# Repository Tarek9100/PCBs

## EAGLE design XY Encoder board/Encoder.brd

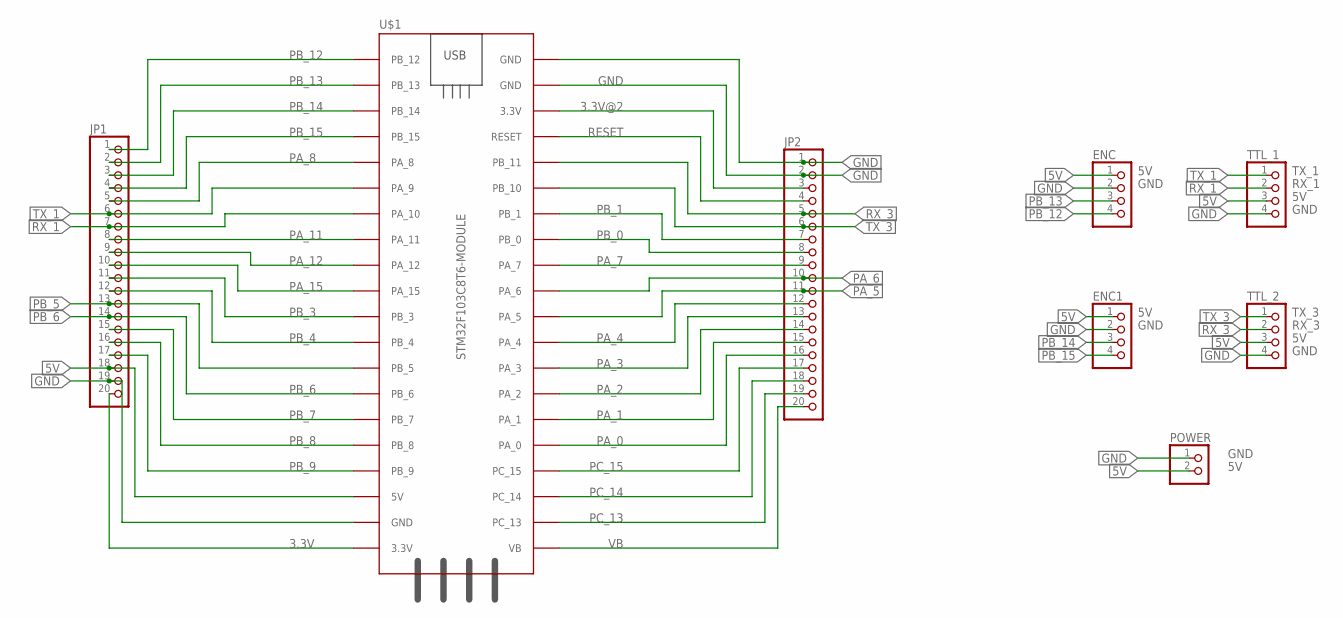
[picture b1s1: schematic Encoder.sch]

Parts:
ENC, ENC1: PINHD-4_DATA; 1X04_DATA
JP1, JP2: PINHD-1X20; 1X20
POWER: PINHD-2_DATA; 1X02_DATA
TTL_1, TTL_2: PINHD-4_DATA; 1X04_DATA
U$1: STM32F103C8T6-MODULE

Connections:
3.3V: JP1.20, U$1.3.3V_1 (3.3V)
3.3V@2: JP2.3, U$1.3.3V_2 (3.3V)
5V: ENC.1, ENC1.1, JP1.18, POWER.2, TTL_1.3, TTL_2.3, U$1.5V
GND: ENC.2, ENC1.2, JP1.19, JP2.1, JP2.2, POWER.1, TTL_1.4, TTL_2.4, U$1.GND_1 (GND), U$1.GND_2 (GND), U$1.GND_3 (GND)
PA_0: JP2.16, U$1.PA_0
PA_1: JP2.15, U$1.PA_1
PA_2: JP2.14, U$1.PA_2
PA_3: JP2.13, U$1.PA_3
PA_4: JP2.12, U$1.PA_4
PA_5: JP2.11, U$1.PA_5
PA_6: JP2.10, U$1.PA_6
PA_7: JP2.9, U$1.PA_7
PA_8: JP1.5, U$1.PA_8
PA_11: JP1.8, U$1.PA_11
PA_12: JP1.9, U$1.PA_12
PA_15: JP1.10, U$1.PA_15
PB_0: JP2.8, U$1.PB_0
PB_1: JP2.7, U$1.PB_1
PB_3: JP1.11, U$1.PB_3
PB_4: JP1.12, U$1.PB_4
PB_5: JP1.13, U$1.PB_5
PB_6: JP1.14, U$1.PB_6
PB_7: JP1.15, U$1.PB_7
PB_8: JP1.16, U$1.PB_8
PB_9: JP1.17, U$1.PB_9
PB_12: ENC.4, JP1.1, U$1.PB_12
PB_13: ENC.3, JP1.2, U$1.PB_13
PB_14: ENC1.3, JP1.3, U$1.PB_14
PB_15: ENC1.4, JP1.4, U$1.PB_15
PC_13: JP2.19, U$1.PC_13
PC_14: JP2.18, U$1.PC_14
PC_15: JP2.17, U$1.PC_15
RESET: JP2.4, U$1.RESET
RX_1: JP1.7, TTL_1.2, U$1.PA_10
RX_3: JP2.5, TTL_2.2, U$1.PB_11
TX_1: JP1.6, TTL_1.1, U$1.PA_9
TX_3: JP2.6, TTL_2.1, U$1.PB_10
VB: JP2.20, U$1.VB

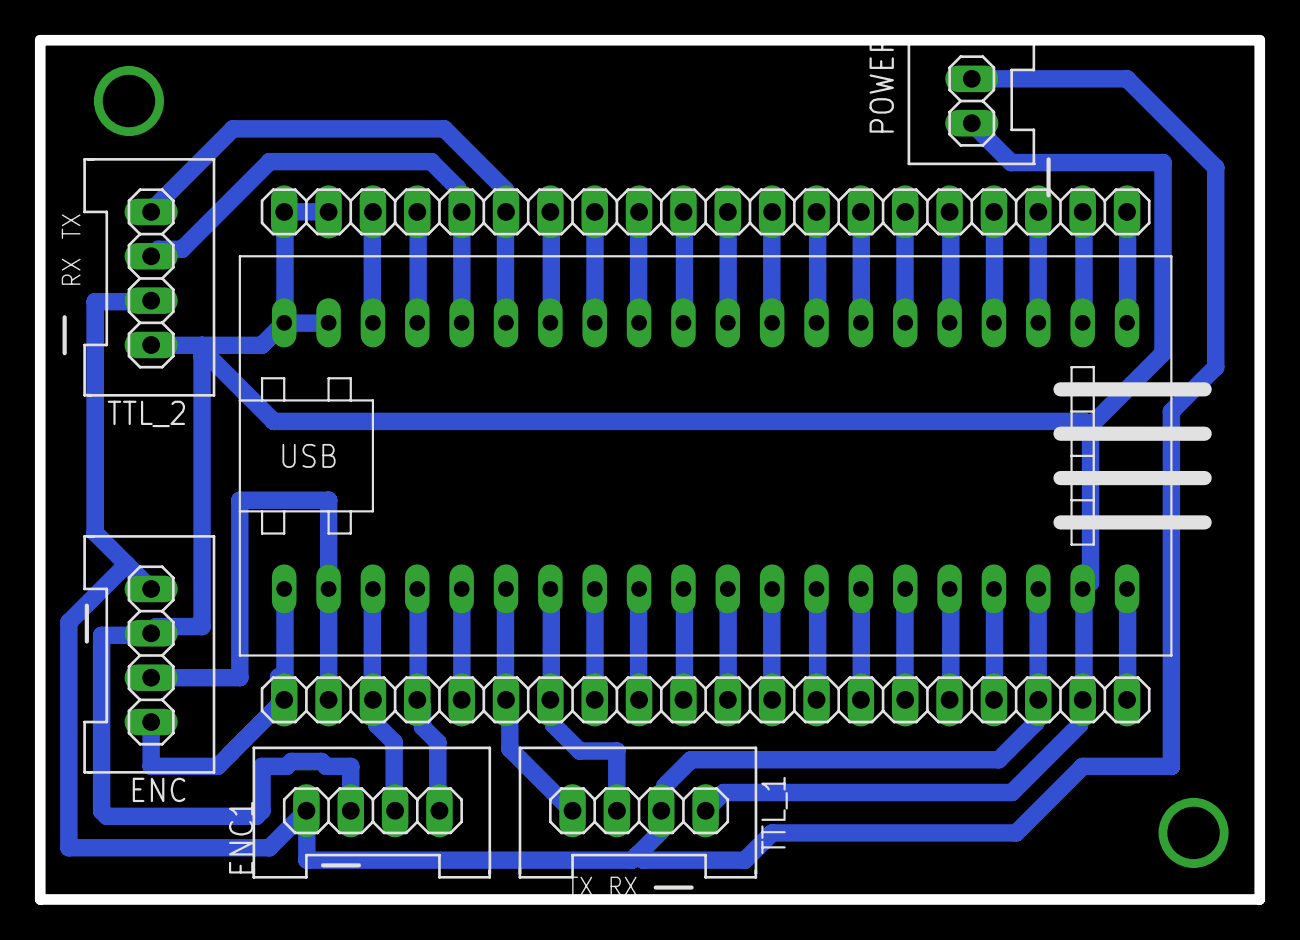
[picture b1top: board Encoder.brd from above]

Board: 2 copper layers, 69.8 x 49.2 mm, 8 parts (0 on the bottom side), 38 nets.

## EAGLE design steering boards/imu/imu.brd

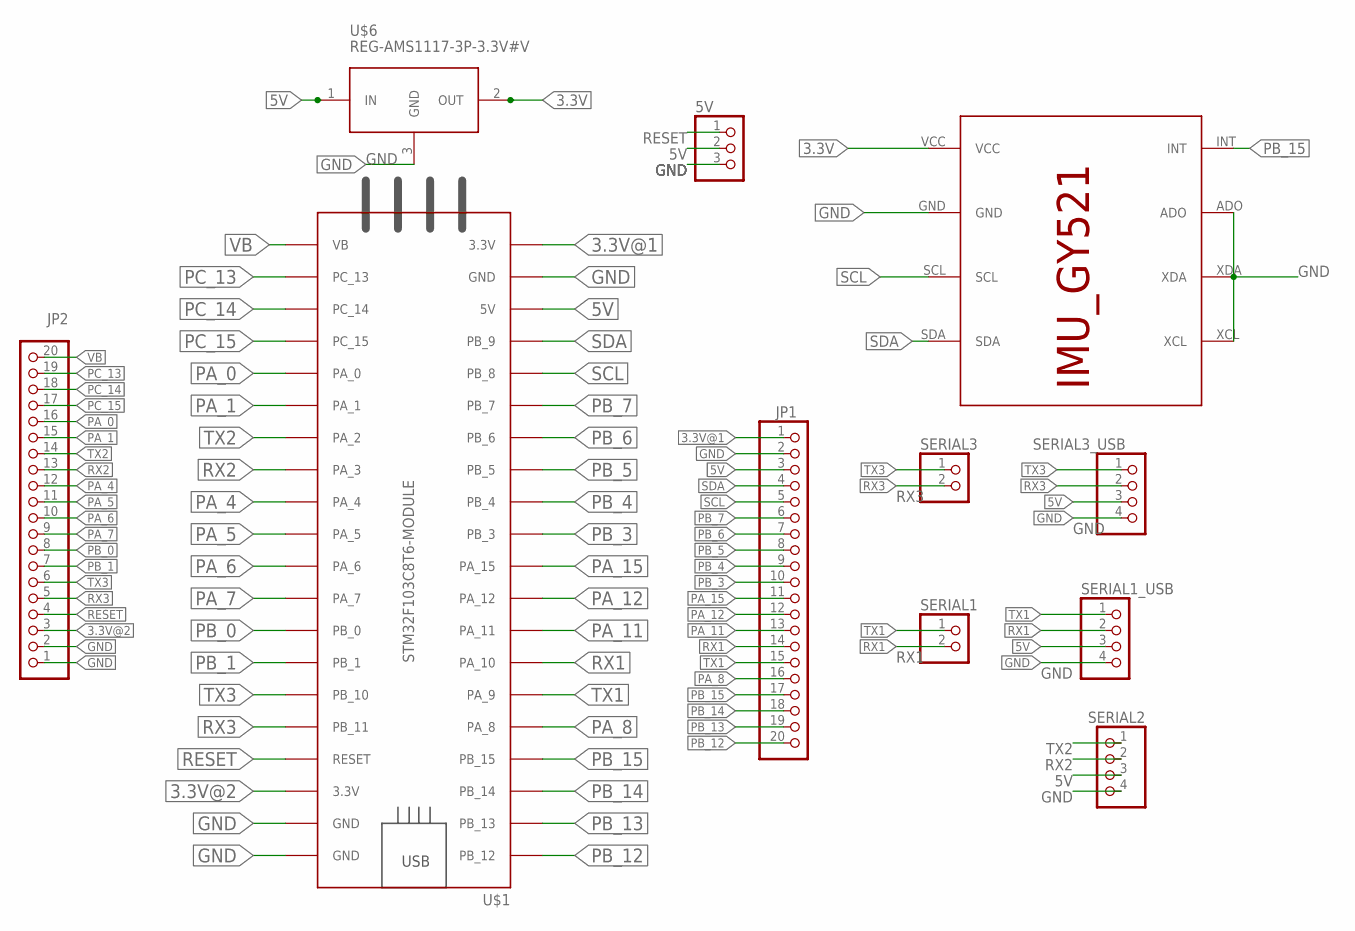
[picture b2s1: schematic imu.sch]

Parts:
5V: PINHD-3_DATA; 1X03_DATA
JP1, JP2: PINHD-1X20; 1X20
SERIAL1, SERIAL3: PINHD-2_DATA; 1X02_DATA
SERIAL1_USB, SERIAL2, SERIAL3_USB: PINHD-4_DATA; 1X04_DATA
U$1: STM32F103C8T6-MODULE
U$2: IMU_ROBOCON_GY521; IMU_GY521
U$6: REG-AMS1117-3P-3.3V#V; REG-AMS1117-3P#V

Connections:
3.3V: U$2.VCC, U$6.2 (OUT)
3.3V@1: JP1.1, U$1.3.3V_1 (3.3V)
3.3V@2: JP2.3, U$1.3.3V_2 (3.3V)
5V: 5V.2, JP1.3, SERIAL1_USB.3, SERIAL2.3, SERIAL3_USB.3, U$1.5V, U$6.1 (IN)
GND: 5V.3, JP1.2, JP2.1, JP2.2, SERIAL1_USB.4, SERIAL2.4, SERIAL3_USB.4, U$1.GND_1 (GND), U$1.GND_2 (GND), U$1.GND_3 (GND), U$2.ADO, U$2.GND, U$2.XCL, U$2.XDA, U$6.3 (GND)
PA_0: JP2.16, U$1.PA_0
PA_1: JP2.15, U$1.PA_1
PA_4: JP2.12, U$1.PA_4
PA_5: JP2.11, U$1.PA_5
PA_6: JP2.10, U$1.PA_6
PA_7: JP2.9, U$1.PA_7
PA_8: JP1.16, U$1.PA_8
PA_11: JP1.13, U$1.PA_11
PA_12: JP1.12, U$1.PA_12
PA_15: JP1.11, U$1.PA_15
PB_0: JP2.8, U$1.PB_0
PB_1: JP2.7, U$1.PB_1
PB_3: JP1.10, U$1.PB_3
PB_4: JP1.9, U$1.PB_4
PB_5: JP1.8, U$1.PB_5
PB_6: JP1.7, U$1.PB_6
PB_7: JP1.6, U$1.PB_7
PB_12: JP1.20, U$1.PB_12
PB_13: JP1.19, U$1.PB_13
PB_14: JP1.18, U$1.PB_14
PB_15: JP1.17, U$1.PB_15, U$2.INT
PC_13: JP2.19, U$1.PC_13
PC_14: JP2.18, U$1.PC_14
PC_15: JP2.17, U$1.PC_15
RESET: 5V.1, JP2.4, U$1.RESET
RX1: JP1.14, SERIAL1.2, SERIAL1_USB.2, U$1.PA_10
RX2: JP2.13, SERIAL2.2, U$1.PA_3
RX3: JP2.5, SERIAL3.2, SERIAL3_USB.2, U$1.PB_11
SCL: JP1.5, U$1.PB_8, U$2.SCL
SDA: JP1.4, U$1.PB_9, U$2.SDA
TX1: JP1.15, SERIAL1.1, SERIAL1_USB.1, U$1.PA_9
TX2: JP2.14, SERIAL2.1, U$1.PA_2
TX3: JP2.6, SERIAL3.1, SERIAL3_USB.1, U$1.PB_10
VB: JP2.20, U$1.VB

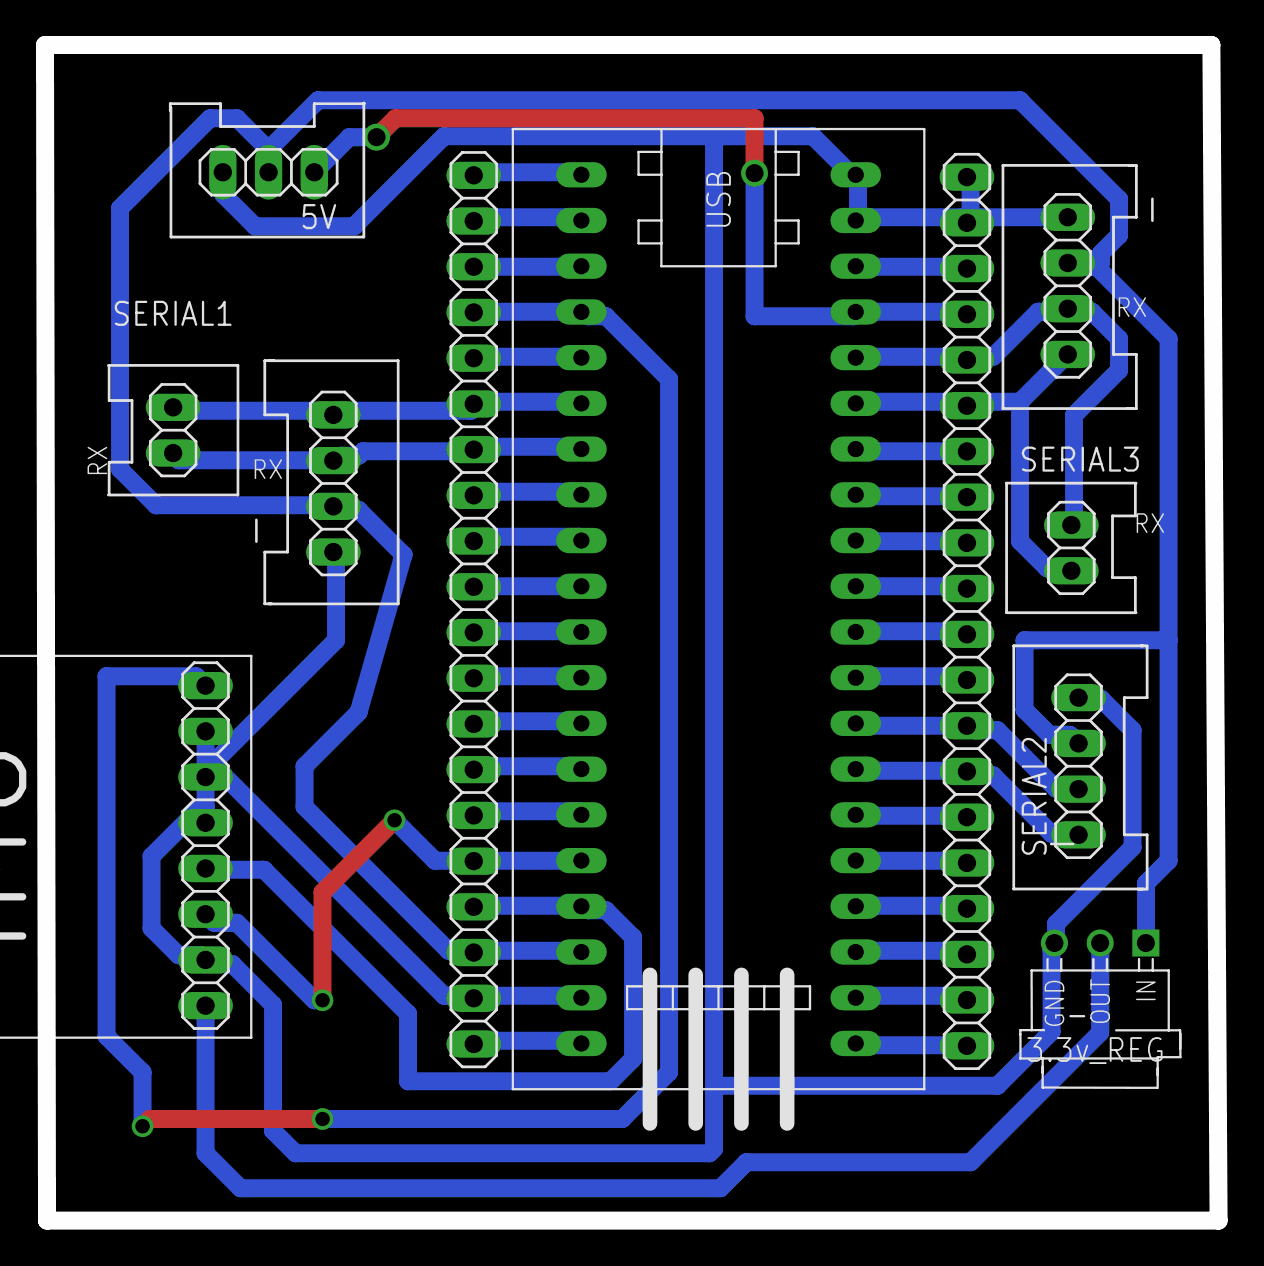
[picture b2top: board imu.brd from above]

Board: 2 copper layers, 65.2 x 65.3 mm, 11 parts (0 on the bottom side), 39 nets.

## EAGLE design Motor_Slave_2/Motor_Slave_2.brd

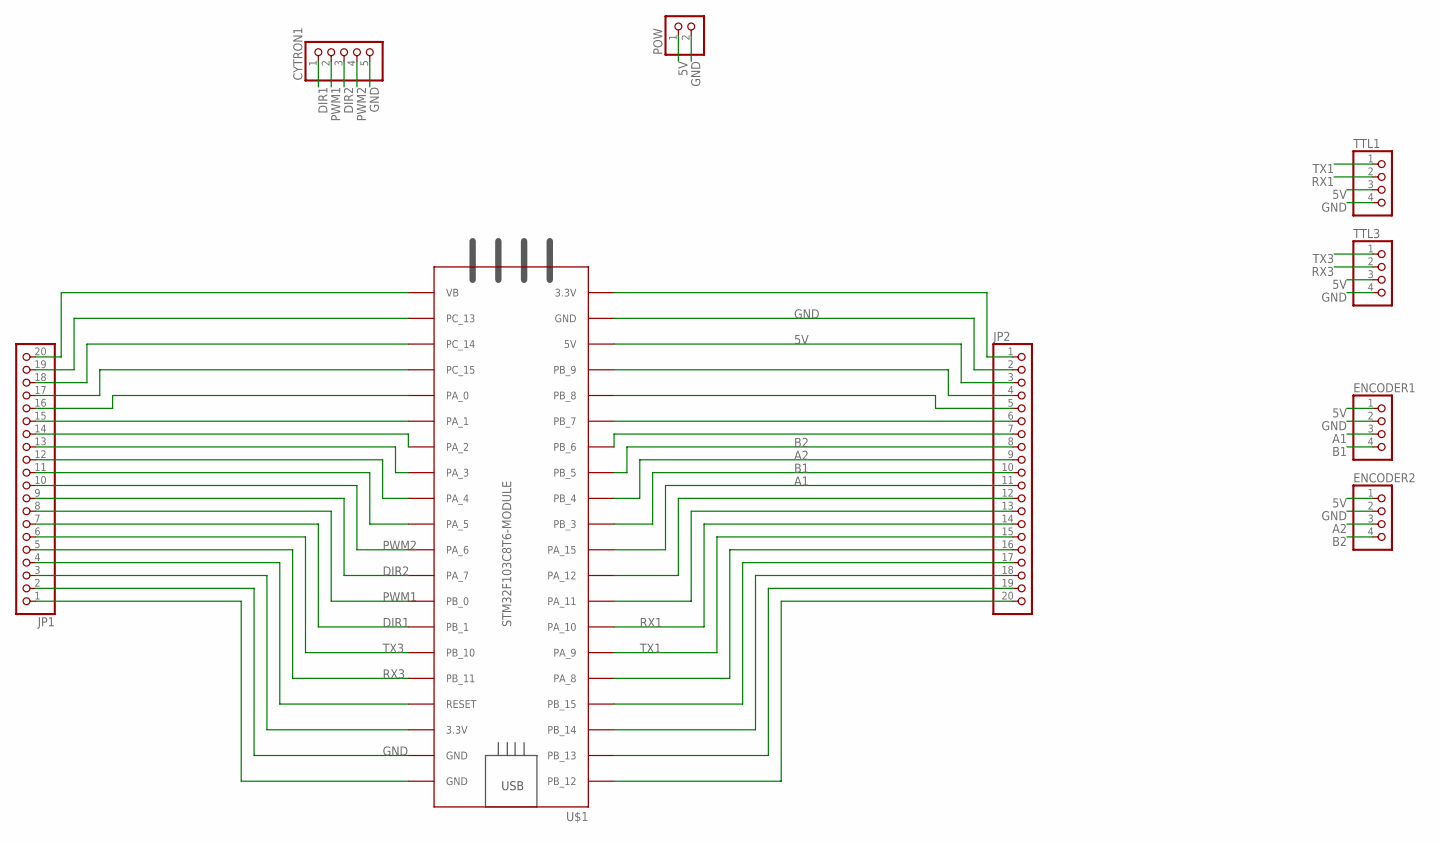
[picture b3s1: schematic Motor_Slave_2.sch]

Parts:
CYTRON1: PINHD-5_DATA; 1X05_DATA
ENCODER1, ENCODER2: PINHD-4_DATA; 1X04_DATA
JP1, JP2: PINHD-1X20; 1X20
POW: PINHD-2_DATA; 1X02_DATA
TTL1, TTL3: PINHD-4_DATA; 1X04_DATA
U$1: STM32F103C8T6-MODULE

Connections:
5V: ENCODER1.1, ENCODER2.1, JP2.3, POW.1, TTL1.3, TTL3.3, U$1.5V
A1: ENCODER1.3, JP2.11, U$1.PA_15
A2: ENCODER2.3, JP2.9, U$1.PB_4
A3: JP2.7, U$1.PB_6
A4: JP2.5, U$1.PB_8
B1: ENCODER1.4, JP2.10, U$1.PB_3
B2: ENCODER2.4, JP2.8, U$1.PB_5
B3: JP2.6, U$1.PB_7
B4: JP2.4, U$1.PB_9
DIR1: CYTRON1.1, JP1.7, U$1.PB_1
DIR2: CYTRON1.3, JP1.9, U$1.PA_7
DIR3: JP1.13, U$1.PA_3
DIR4: JP1.15, U$1.PA_1
GND: CYTRON1.5, ENCODER1.2, ENCODER2.2, JP1.2, JP2.2, POW.2, TTL1.4, TTL3.4, U$1.GND_1 (GND), U$1.GND_2 (GND)
unnamed: JP1.20, U$1.VB
unnamed: JP1.19, U$1.PC_13
unnamed: JP1.18, U$1.PC_14
unnamed: JP1.17, U$1.PC_15
unnamed: JP1.12, U$1.PA_4
unnamed: JP1.11, U$1.PA_5
unnamed: JP1.4, U$1.RESET
unnamed: JP1.3, U$1.3.3V_2 (3.3V)
unnamed: JP1.1, U$1.GND_3 (GND)
unnamed: JP2.1, U$1.3.3V_1 (3.3V)
unnamed: JP2.12, U$1.PA_12
unnamed: JP2.13, U$1.PA_11
unnamed: JP2.16, U$1.PA_8
unnamed: JP2.17, U$1.PB_15
unnamed: JP2.18, U$1.PB_14
unnamed: JP2.19, U$1.PB_13
unnamed: JP2.20, U$1.PB_12
PWM1: CYTRON1.2, JP1.8, U$1.PB_0
PWM2: CYTRON1.4, JP1.10, U$1.PA_6
PWM3: JP1.14, U$1.PA_2
PWM4: JP1.16, U$1.PA_0
RX1: JP2.14, TTL1.2, U$1.PA_10
RX3: JP1.5, TTL3.2, U$1.PB_11
TX1: JP2.15, TTL1.1, U$1.PA_9
TX3: JP1.6, TTL3.1, U$1.PB_10

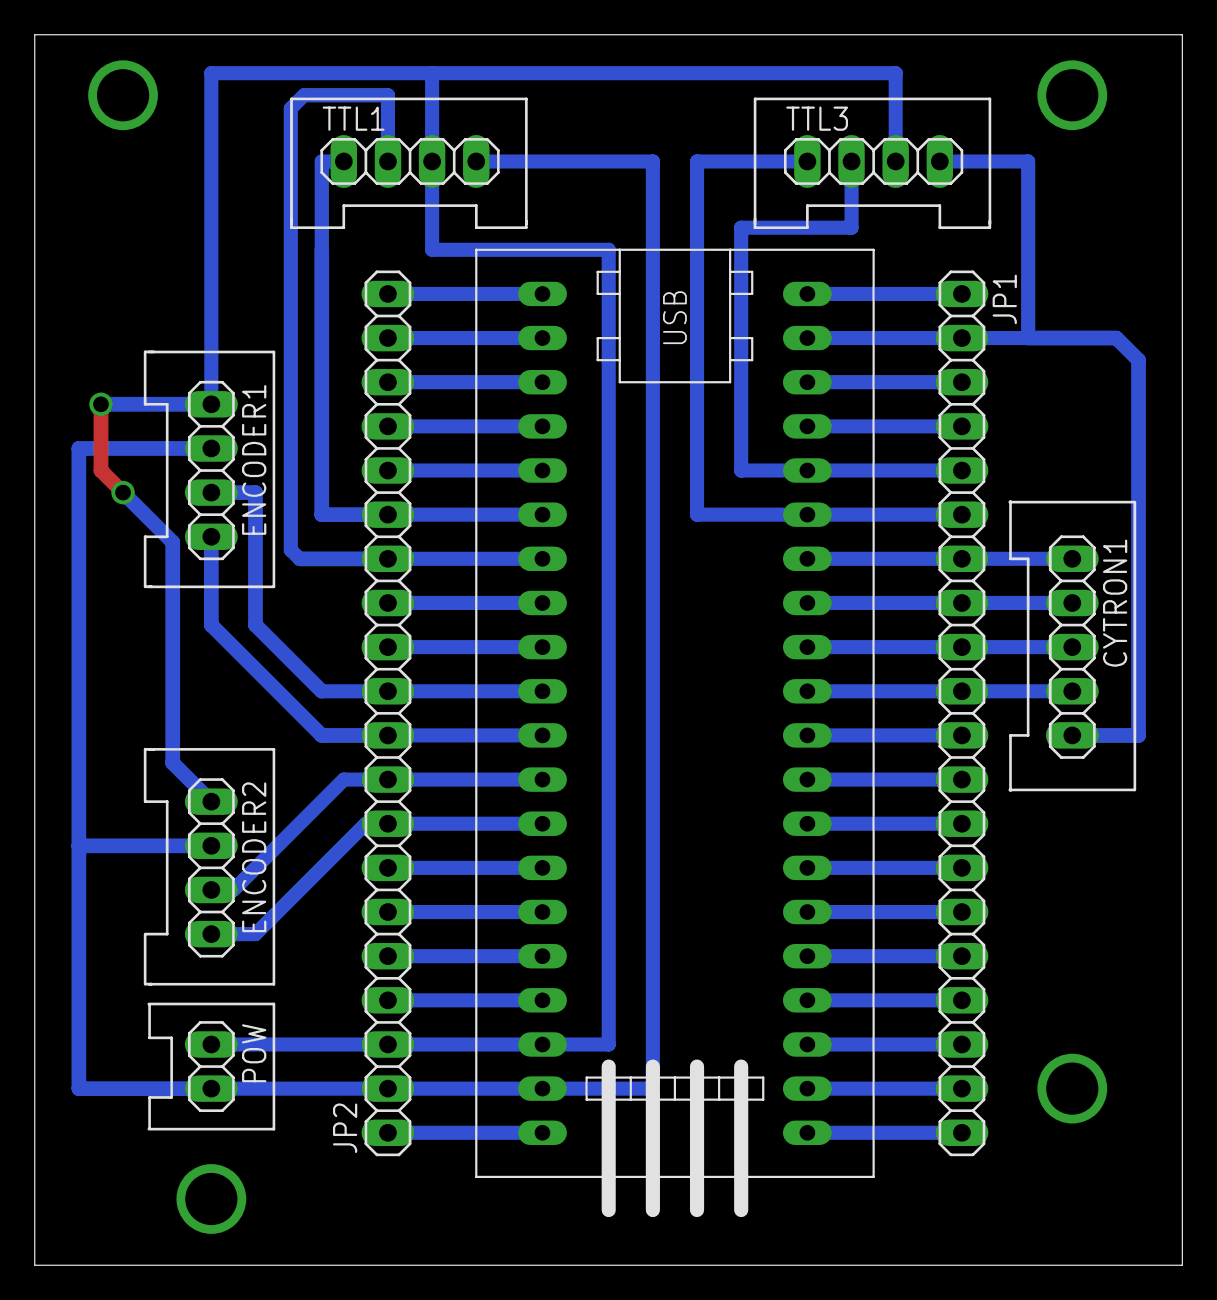
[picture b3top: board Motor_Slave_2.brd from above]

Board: 2 copper layers, 66.0 x 70.8 mm, 9 parts (0 on the bottom side), 39 nets.

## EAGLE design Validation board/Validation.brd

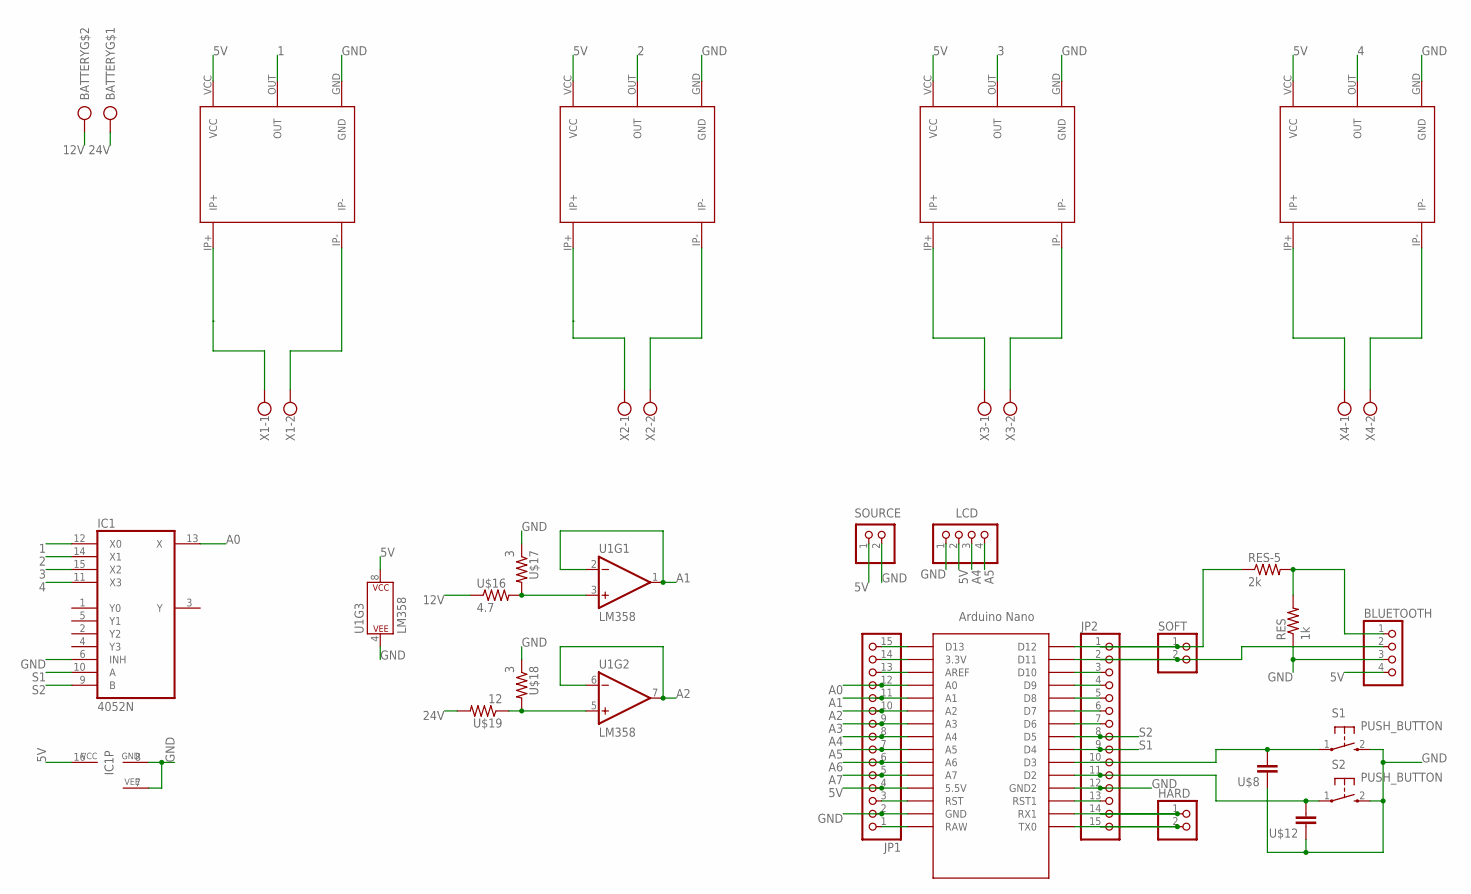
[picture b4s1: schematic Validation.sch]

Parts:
BATTERY: CON_PTR_2; AK300/2
BLUETOOTH: PINHD-4_DATA; 1X04_DATA
HARD: PINHD-2_DATA; 1X02_DATA
IC1: 4052N; DIL16
JP1, JP2: PINHD-1X15; 1X15
LCD: PINHD-4_DATA; 1X04_DATA
RES: 1k; 0204/5
RES-5: 2k; 0204/5
S1, S2: PUSH_BUTTON; B3F-10XX
SOFT: PINHD-2_DATA; 1X02_DATA
SOURCE: PINHD-2_DATA; 1X02_DATA
U1: LM358; DIP08
U$1, U$5, U$9, U$13: ASC712_MODULE
U$4: ARDUINO_NANO; NANO
U$8, U$12: CAPACITOR; C025-025X050
U$16: 4.7; 0204/7
U$17, U$18: 3; 0204/7
U$19: 12; 0204/7
X1, X2, X3, X4: ROSTA.POWER; W239-302

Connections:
1: IC1.12 (X0), U$1.OUT
2: IC1.14 (X1), U$5.OUT
3: IC1.15 (X2), U$9.OUT
4: IC1.11 (X3), U$13.OUT
5V: BLUETOOTH.4, IC1.16 (VCC), JP1.4, LCD.2, SOURCE.1, U1.8 (P$V+), U$1.VCC, U$4.5V (5.5V), U$5.VCC, U$9.VCC, U$13.VCC
12V: BATTERY.2, U$16.1
24V: BATTERY.1, U$19.2
A0: IC1.13 (X), JP1.12, U$4.A0
A1: JP1.11, U1.1 (OUT), U1.2 (-IN), U$4.A1
A2: JP1.10, U1.6 (-IN), U1.7 (OUT), U$4.A2
A3: JP1.9, U$4.A3
A4: JP1.8, LCD.3, U$4.A4
A5: JP1.7, LCD.4, U$4.A5
A6: JP1.6, U$4.A6
A7: JP1.5, U$4.A7
GND: BLUETOOTH.3, IC1.6 (INH), IC1.7 (VEE), IC1.8 (GND), JP1.2, JP2.12, LCD.1, RES.1, S1.2 (S), S2.2 (S), SOURCE.2, U1.4 (P$V-), U$1.GND, U$4.GND, U$4.GND1 (GND2), U$5.GND, U$8.1, U$9.GND, U$12.1, U$13.GND, U$17.1, U$18.1
unnamed: U$1.IP+, X1.1
unnamed: JP1.1, U$4.RAW
unnamed: U$1.IP-, X1.2
unnamed: U$5.IP+, X2.1
unnamed: U$5.IP-, X2.2
unnamed: U$13.IP-, X4.2
unnamed: U$9.IP+, X3.1
unnamed: U$9.IP-, X3.2
unnamed: U1.3 (+IN), U$16.2, U$17.2
unnamed: U$13.IP+, X4.1
unnamed: JP1.3, U$4.RST
unnamed: BLUETOOTH.1, RES.2, RES-5.2
unnamed: U1.5 (+IN), U$18.2, U$19.1
unnamed: JP1.13, U$4.AREF
unnamed: JP1.14, U$4.3.3V
unnamed: JP1.15, U$4.D13
unnamed: JP2.1, RES-5.1, SOFT.1, U$4.D12
unnamed: BLUETOOTH.2, JP2.2, SOFT.2, U$4.D11
unnamed: JP2.3, U$4.D10
unnamed: JP2.4, U$4.D9
unnamed: JP2.5, U$4.D8
unnamed: JP2.6, U$4.D7
unnamed: JP2.7, U$4.D6
unnamed: JP2.10, S1.1, U$4.D3, U$8.2
unnamed: JP2.11, S2.1, U$4.D2, U$12.2
unnamed: JP2.13, U$4.RST1
unnamed: HARD.1, JP2.14, U$4.RX1
unnamed: HARD.2, JP2.15, U$4.TX0
S1: IC1.10 (A), JP2.9, U$4.D4
S2: IC1.9 (B), JP2.8, U$4.D5

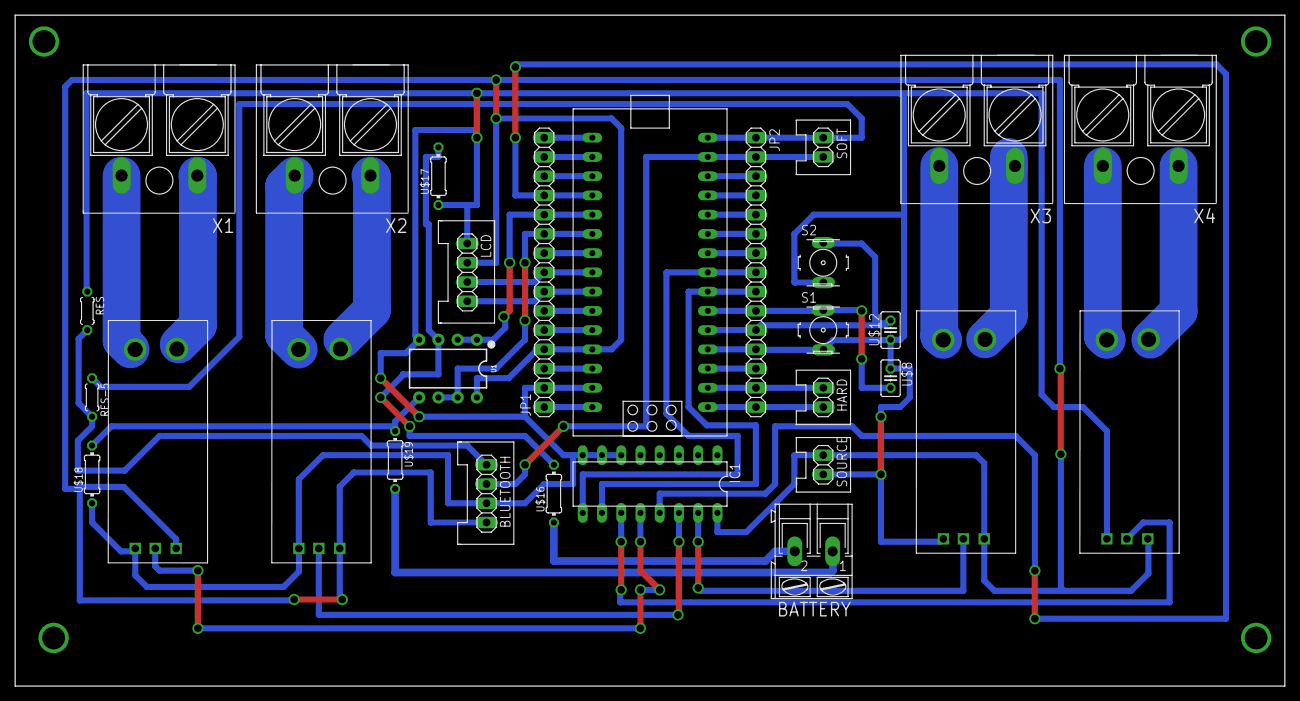
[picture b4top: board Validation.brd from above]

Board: 2 copper layers, 167.6 x 88.6 mm, 29 parts (0 on the bottom side), 46 nets.

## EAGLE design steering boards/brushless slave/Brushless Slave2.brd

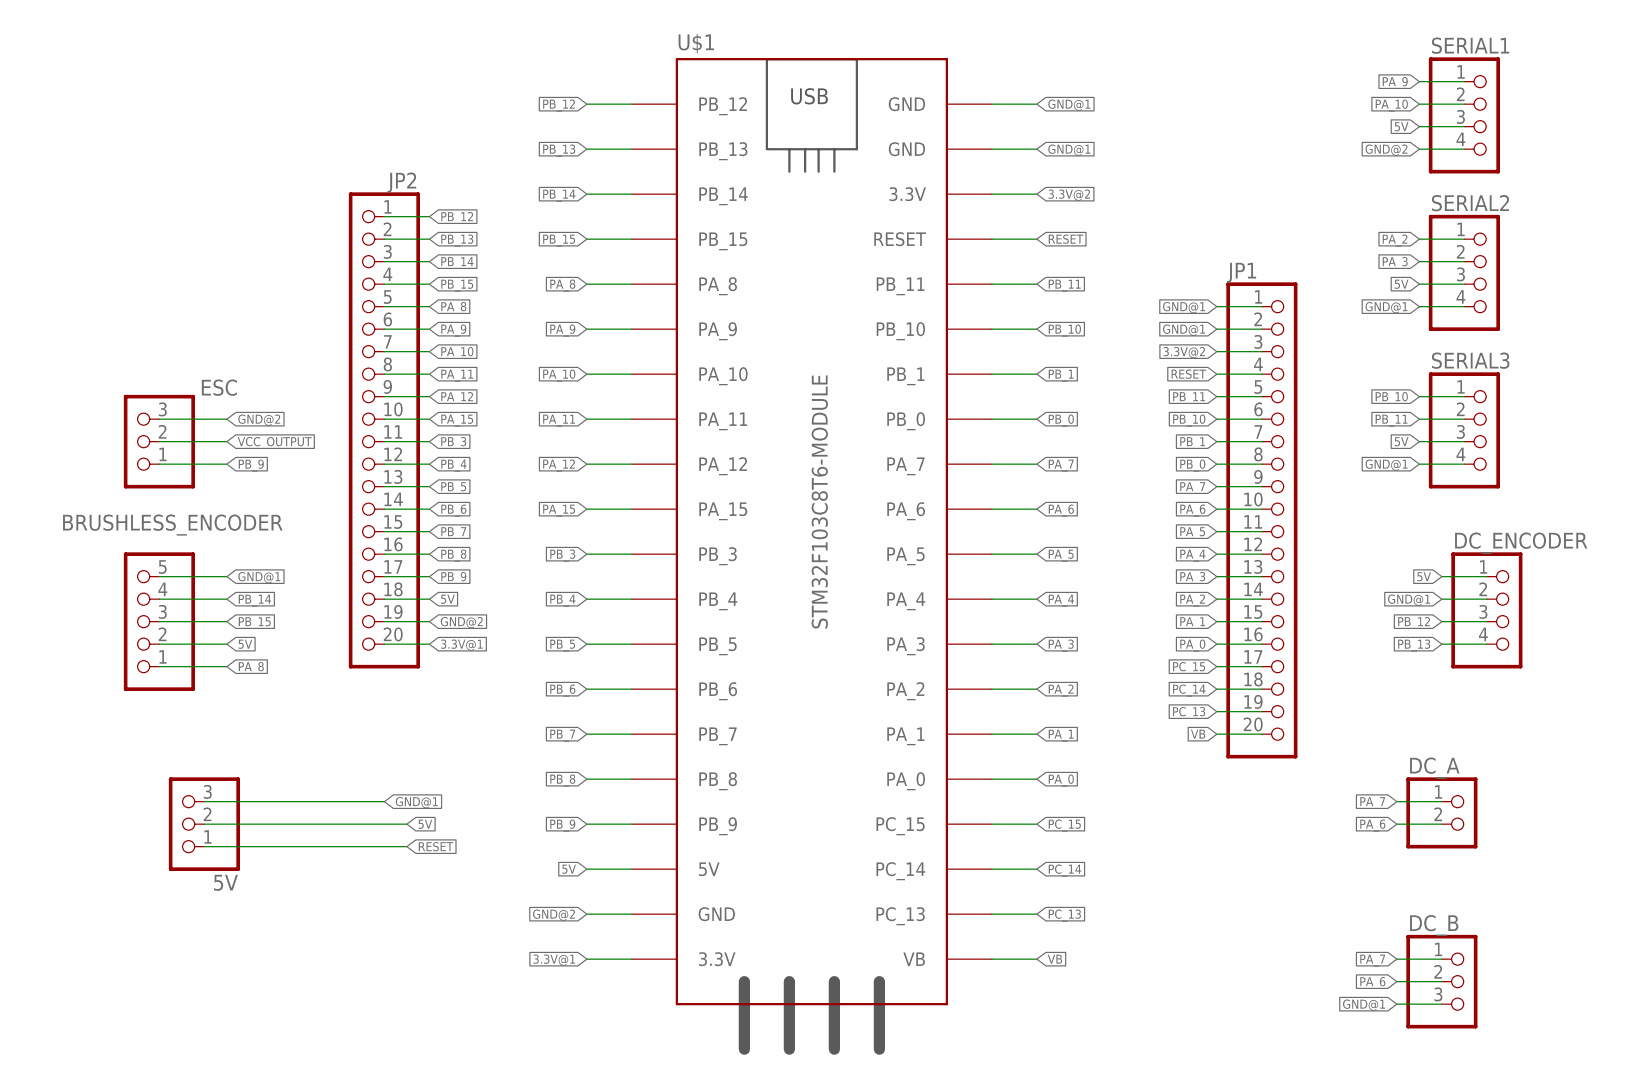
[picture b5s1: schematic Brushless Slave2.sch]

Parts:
5V: PINHD-3_DATA; 1X03_DATA
BRUSHLESS_ENCODER: PINHD-5_DATA; 1X05_DATA
DC_A: PINHD-2_DATA; 1X02_DATA
DC_B: PINHD-3_DATA; 1X03_DATA
DC_ENCODER: PINHD-4_DATA; 1X04_DATA
ESC: PINHD-3_DATA; 1X03_DATA
JP1, JP2: PINHD-1X20; 1X20
SERIAL1, SERIAL2, SERIAL3: PINHD-4_DATA; 1X04_DATA
U$1: STM32F103C8T6-MODULE

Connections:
3.3V@1: JP2.20, U$1.3.3V_1 (3.3V)
3.3V@2: JP1.3, U$1.3.3V_2 (3.3V)
5V: 5V.2, BRUSHLESS_ENCODER.2, DC_ENCODER.1, JP2.18, SERIAL1.3, SERIAL2.3, SERIAL3.3, U$1.5V
GND@1: 5V.3, BRUSHLESS_ENCODER.5, DC_B.3, DC_ENCODER.2, JP1.1, JP1.2, SERIAL2.4, SERIAL3.4, U$1.GND_2 (GND), U$1.GND_3 (GND)
GND@2: ESC.3, JP2.19, SERIAL1.4, U$1.GND_1 (GND)
PA_0: JP1.16, U$1.PA_0
PA_1: JP1.15, U$1.PA_1
PA_2: JP1.14, SERIAL2.1, U$1.PA_2
PA_3: JP1.13, SERIAL2.2, U$1.PA_3
PA_4: JP1.12, U$1.PA_4
PA_5: JP1.11, U$1.PA_5
PA_6: DC_A.2, DC_B.2, JP1.10, U$1.PA_6
PA_7: DC_A.1, DC_B.1, JP1.9, U$1.PA_7
PA_8: BRUSHLESS_ENCODER.1, JP2.5, U$1.PA_8
PA_9: JP2.6, SERIAL1.1, U$1.PA_9
PA_10: JP2.7, SERIAL1.2, U$1.PA_10
PA_11: JP2.8, U$1.PA_11
PA_12: JP2.9, U$1.PA_12
PA_15: JP2.10, U$1.PA_15
PB_0: JP1.8, U$1.PB_0
PB_1: JP1.7, U$1.PB_1
PB_3: JP2.11, U$1.PB_3
PB_4: JP2.12, U$1.PB_4
PB_5: JP2.13, U$1.PB_5
PB_6: JP2.14, U$1.PB_6
PB_7: JP2.15, U$1.PB_7
PB_8: JP2.16, U$1.PB_8
PB_9: ESC.1, JP2.17, U$1.PB_9
PB_10: JP1.6, SERIAL3.1, U$1.PB_10
PB_11: JP1.5, SERIAL3.2, U$1.PB_11
PB_12: DC_ENCODER.3, JP2.1, U$1.PB_12
PB_13: DC_ENCODER.4, JP2.2, U$1.PB_13
PB_14: BRUSHLESS_ENCODER.4, JP2.3, U$1.PB_14
PB_15: BRUSHLESS_ENCODER.3, JP2.4, U$1.PB_15
PC_13: JP1.19, U$1.PC_13
PC_14: JP1.18, U$1.PC_14
PC_15: JP1.17, U$1.PC_15
RESET: 5V.1, JP1.4, U$1.RESET
VB: JP1.20, U$1.VB
VCC_OUTPUT: ESC.2

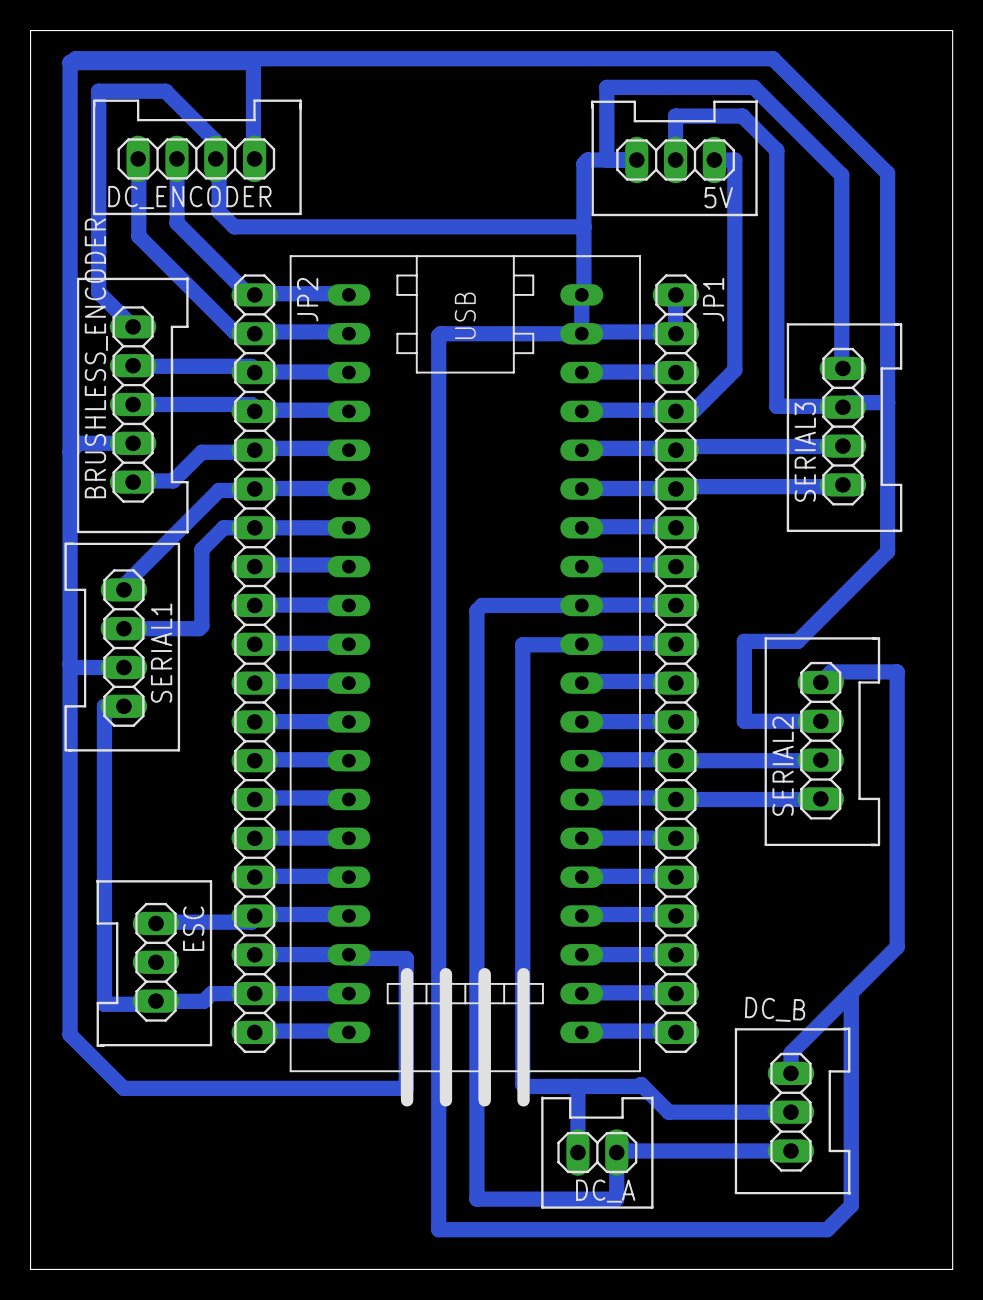
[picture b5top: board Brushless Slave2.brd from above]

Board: 2 copper layers, 60.3 x 81.1 mm, 12 parts (0 on the bottom side), 39 nets.

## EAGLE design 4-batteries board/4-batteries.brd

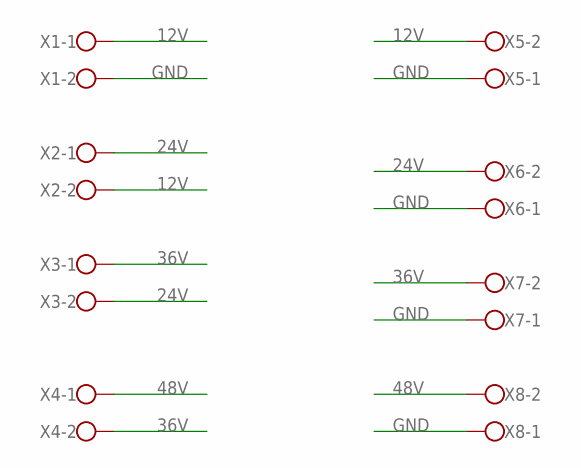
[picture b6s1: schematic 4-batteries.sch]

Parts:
X1, X2, X3, X4, X5, X6, X7, X8: ROSTA.POWER; W239-302

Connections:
12V: X1.1, X2.2, X5.2
24V: X2.1, X3.2, X6.2
36V: X3.1, X4.2, X7.2
48V: X4.1, X8.2
GND: X1.2, X5.1, X6.1, X7.1, X8.1

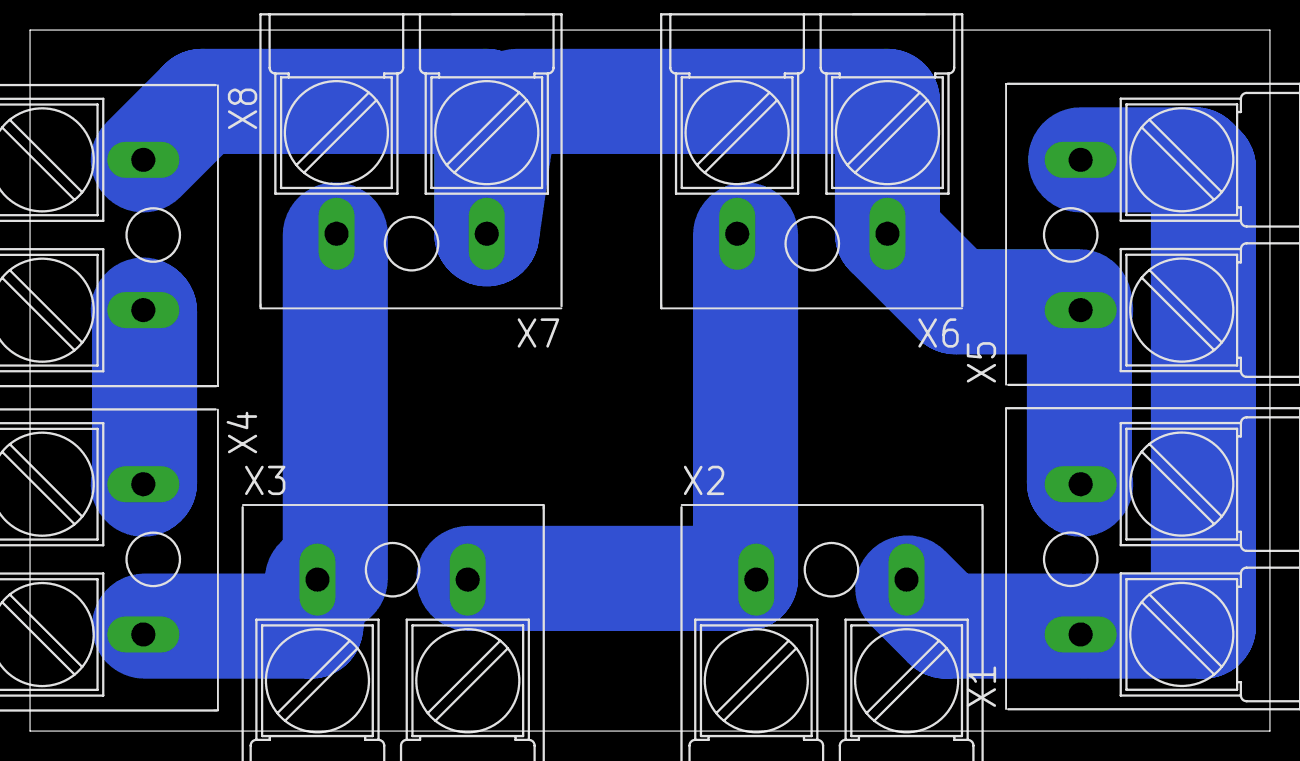
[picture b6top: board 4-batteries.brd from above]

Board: 2 copper layers, 82.5 x 46.7 mm, 8 parts (0 on the bottom side), 5 nets.

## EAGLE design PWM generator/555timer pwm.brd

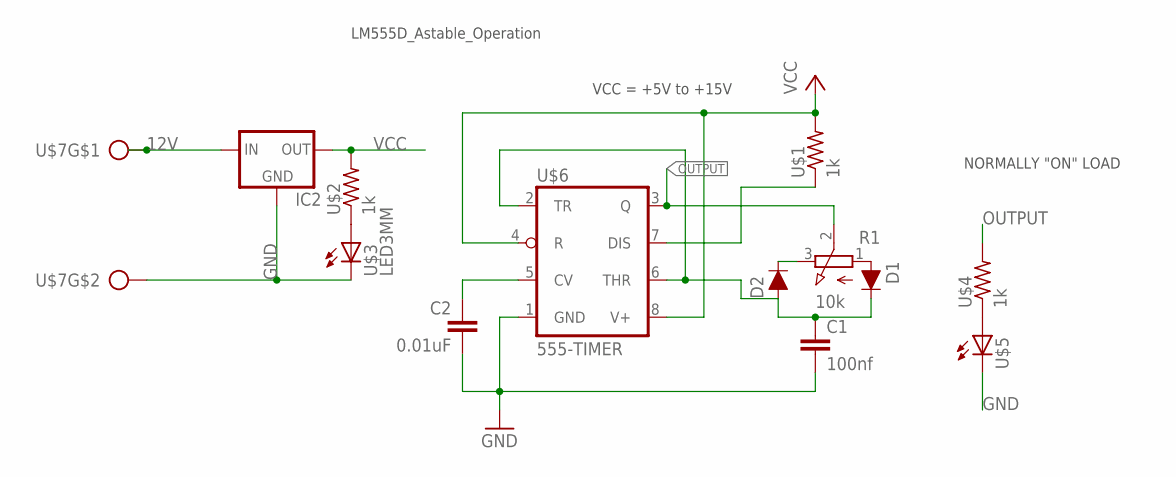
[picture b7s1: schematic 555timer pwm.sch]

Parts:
C1: 100nf; C025-025X050
C2: 0.01uF; C025-025X050
D1, D2: 200mA/100V/1V; DIODE-1N4148
IC2: 78XXS
R1: 10k; 3RP/1610N
U$1, U$2, U$4: 1k; 0204/5
U$3, U$5: LED3MM
U$6: 555-TIMER; DIL08
U$7: CON_PTR_2; AK300/2

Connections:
12V: IC2.IN, U$7.1
GND: C1.2, C2.2, IC2.GND, U$3.K (C), U$5.K (C), U$6.1 (GND), U$7.2
unnamed: D1.A, R1.1 (A)
unnamed: C1.1, D1.C, D2.A, U$6.2 (TR), U$6.6 (THR)
unnamed: C2.1, U$6.5 (CV)
unnamed: D2.C, R1.3 (E)
unnamed: U$2.1, U$3.A
unnamed: U$4.1, U$5.A
unnamed: U$1.1, U$6.7 (DIS)
OUTPUT: R1.2 (S), U$4.2, U$6.3 (Q)
VCC: IC2.OUT, U$1.2, U$2.2, U$6.4 (R), U$6.8 (V+)

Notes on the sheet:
NORMALLY "ON" LOAD
LM555D_Astable_Operation
VCC = +5V to +15V

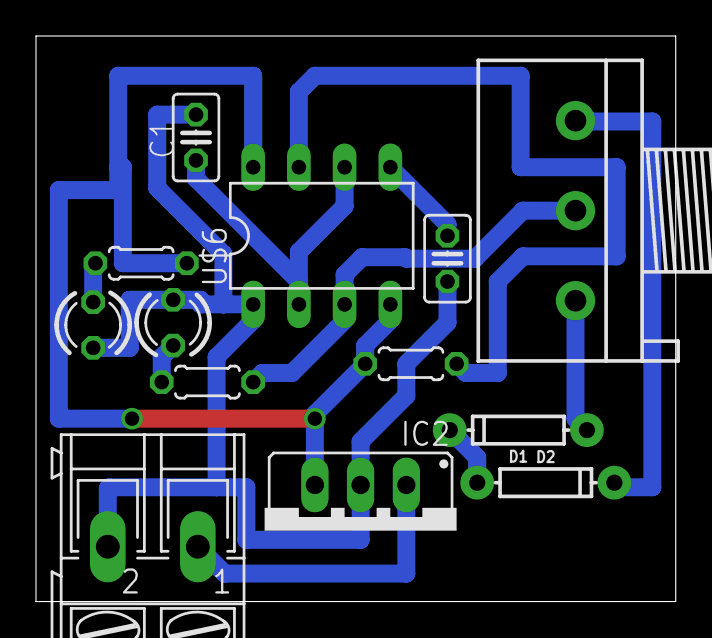
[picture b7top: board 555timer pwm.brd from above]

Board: 2 copper layers, 35.5 x 31.4 mm, 13 parts (0 on the bottom side), 11 nets.

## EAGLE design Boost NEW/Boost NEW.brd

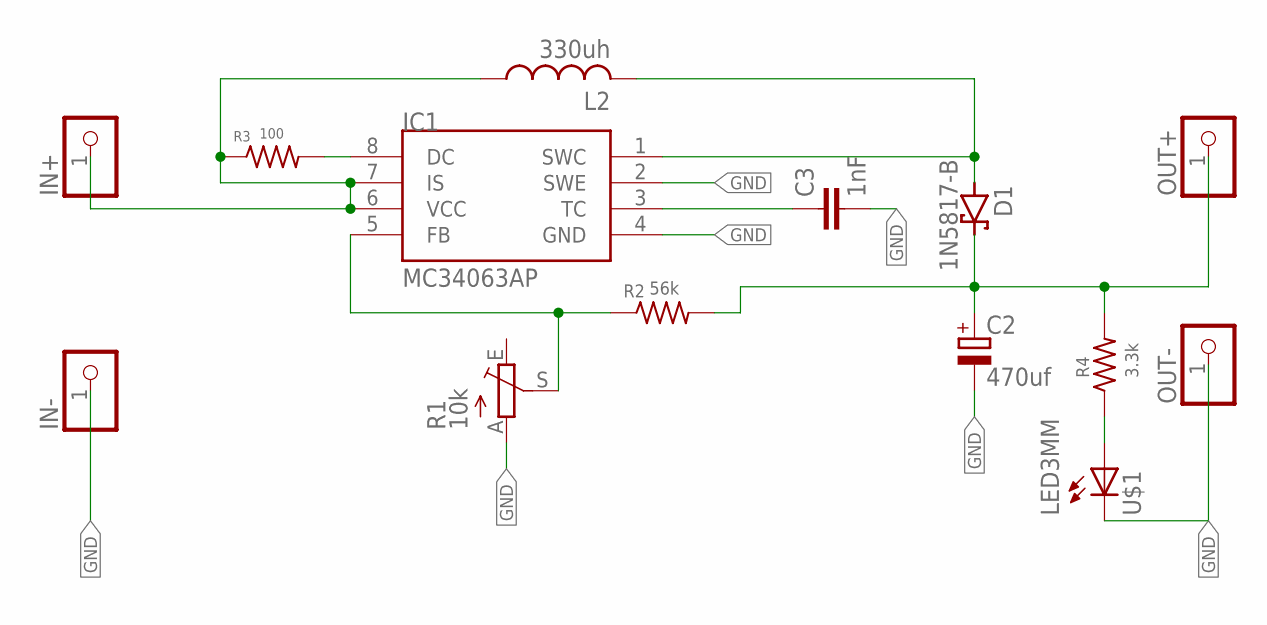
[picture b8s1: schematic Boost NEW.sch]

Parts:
C2: 470uf; E3,5-8
C3: 1nF; C025-025X050
D1: 1N5817-B; DO41-7.6
IC1: MC34063AP; DIL08
IN+: PINHD-1X1; 1X01
IN-: PINHD-1X1; 1X01
L2: 330uh; 0207/10
OUT+: PINHD-1X1; 1X01
OUT-: PINHD-1X1; 1X01
R1: 10k; CA6V
R2: 56k; 0204/7
R3: 100; 0204/7
R4: 3.3k; 0204/7
U$1: LED3MM

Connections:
GND: C2.-, C3.2, IC1.2 (SWE), IC1.4 (GND), IN-.1, OUT-.1, R1.A, U$1.K (C)
IN: C2.+, D1.C, OUT+.1, R2.2, R4.2
unnamed: IC1.6 (VCC), IC1.7 (IS), IN+.1, L2.1, R3.1
unnamed: R4.1, U$1.A
unnamed: D1.A, IC1.1 (SWC), L2.2
unnamed: IC1.5 (FB), R1.S, R2.1
unnamed: C3.1, IC1.3 (TC)
unnamed: IC1.8 (DC), R3.2

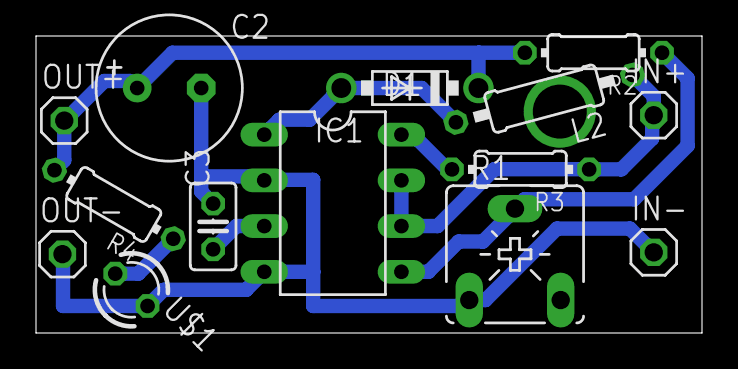
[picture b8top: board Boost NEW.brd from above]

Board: 2 copper layers, 37.0 x 16.5 mm, 14 parts (0 on the bottom side), 8 nets.

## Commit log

2023-09-16 Added all PCBs done since day 1
